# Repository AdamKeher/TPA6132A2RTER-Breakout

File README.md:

# TPA6132A2RTER Breakout
Headphone Amplifier breakout board using TPA6132A2RTER.

## Jack Sense
The board contains an audio jack sensing circuit with inverted output. This can be used to drive something like an enable / mute pin on a speaker amplifier, effectively muting output when a plug is inserted in the jack.

## Amplifier Gain
Pinheaders are provided for user configurable gain control.

## Board Image

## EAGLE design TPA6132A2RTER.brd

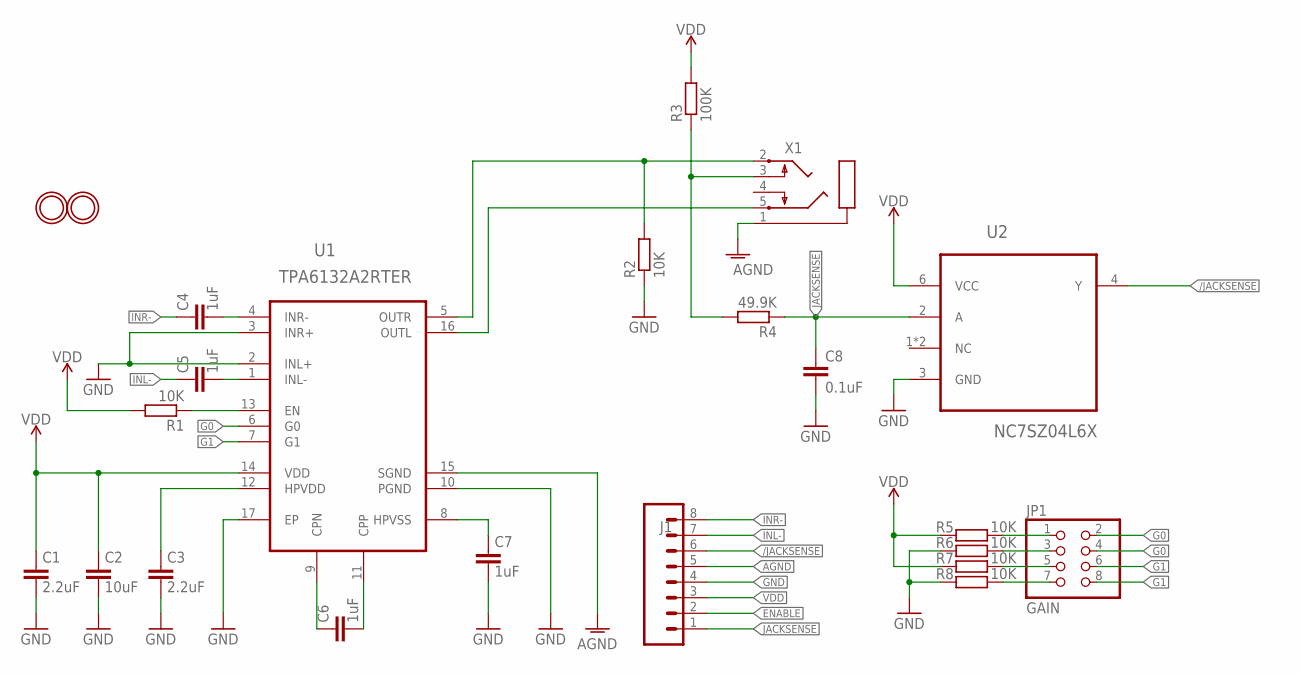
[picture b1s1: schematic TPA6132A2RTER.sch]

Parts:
C1, C3: 2.2uF; C0402K
C2: 10uF; C0402K
C4, C5, C6, C7: 1uF; C0402K
C8: 0.1uF; C0402K
J1: CONN_08NO_SILK_FEMALE_PTH; 1X08_NO_SILK
JP1: GAIN; 2X04
MH1, MH2: MOUNTINGHOLE2.5; MOUNTINGHOLE_2.5_PLATED
R1, R2, R5, R6, R7, R8: 10K; R0402
R3: 100K; R0402
R4: 49.9K; R0402
U1: TPA6132A2RTER; QFN50P300X300X80-16N
U2: NC7SZ04L6X; MICROPAK-6
X1: STEREOJACKSTX3120-5B; STX3100

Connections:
/JACKSENSE: J1.6, U2.4 (Y)
AGND: J1.5, U1.15 (SGND), X1.1
ENABLE: J1.2, R1.1, U1.13 (EN)
G0: JP1.2, JP1.4, U1.6 (G0)
G1: JP1.6, JP1.8, U1.7 (G1)
GND: C1.2, C2.2, C3.2, C7.2, C8.2, J1.4, R2.1, R6.1, R8.1, U1.2 (INL+), U1.3 (INR+), U1.10 (PGND), U1.17 (EP), U2.3 (GND)
INL-: C5.1, J1.7
INR-: C4.1, J1.8
JACKSENSE: C8.1, J1.1, R4.1, U2.2 (A)
unnamed: C6.2, U1.11 (CPP)
unnamed: C6.1, U1.9 (CPN)
unnamed: JP1.3, R6.2
unnamed: JP1.7, R8.2
unnamed: C5.2, U1.1 (INL-)
unnamed: C3.1, U1.12 (HPVDD)
unnamed: C7.1, U1.8 (HPVSS)
unnamed: JP1.1, R5.2
unnamed: JP1.5, R7.2
unnamed: R3.1, R4.2, X1.3
unnamed: C4.2, U1.4 (INR-)
OUTL: U1.16 (OUTL), X1.5
OUTR: R2.2, U1.5 (OUTR), X1.2
VDD: C1.1, C2.1, J1.3, R1.2, R3.2, R5.1, R7.1, U1.14 (VDD), U2.6 (VCC)

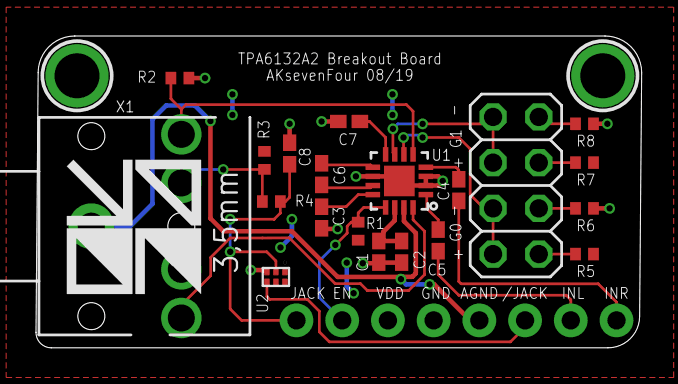
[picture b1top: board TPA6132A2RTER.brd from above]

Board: 2 copper layers, 33.6 x 17.3 mm, 25 parts (1 on the bottom side), 23 nets.

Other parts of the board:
U$1: AK74_LOGO_MEDIUM_TEXTONLY
U$2: AK74_LOGO_MEDIUM_TEXTONLY_SQUARE

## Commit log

2019-08-14 Initial Upload
2019-08-14 Clean up

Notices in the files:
parts and their libraries:
SparkFun-Connectors: Licensing: Creative Commons ShareAlike 4.0 International - https://creativecommons.org/licenses/by-sa/4.0
microbuilder: This work is placed in the public domain, and may be freely used for commercial and non-commercial work with the following conditions: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
